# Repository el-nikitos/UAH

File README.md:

UAH
Драйвер двигателя и нагревателя

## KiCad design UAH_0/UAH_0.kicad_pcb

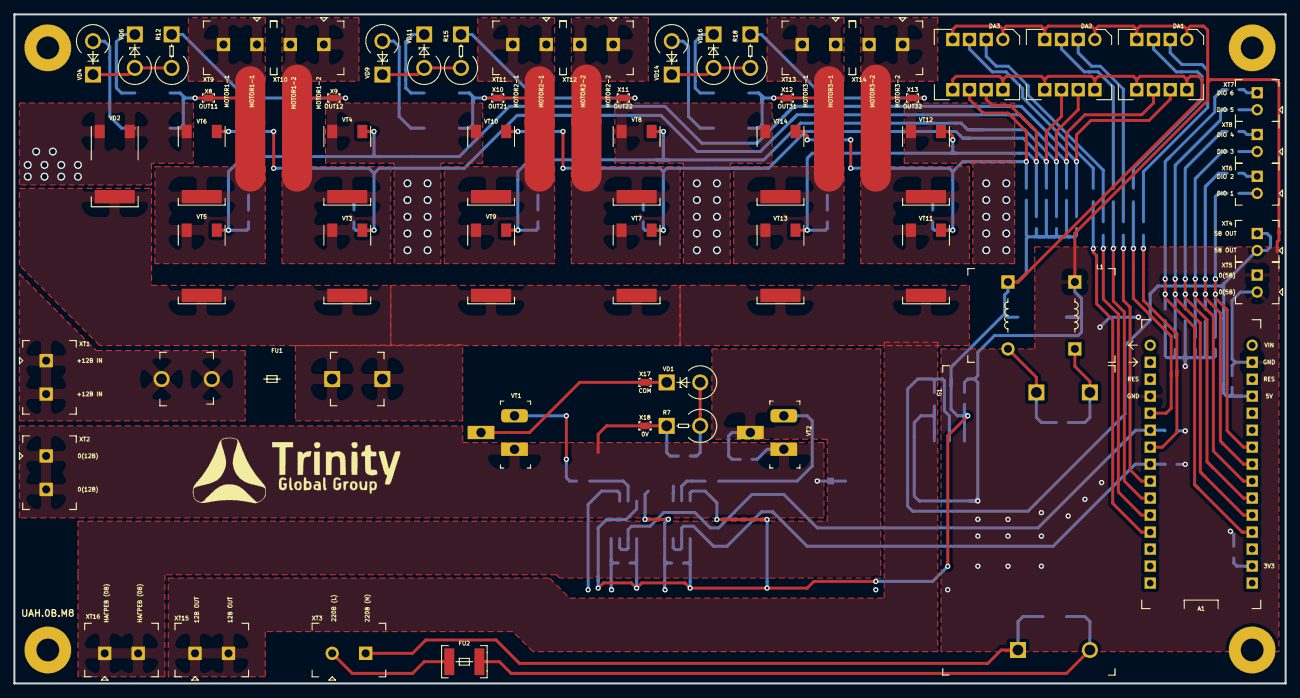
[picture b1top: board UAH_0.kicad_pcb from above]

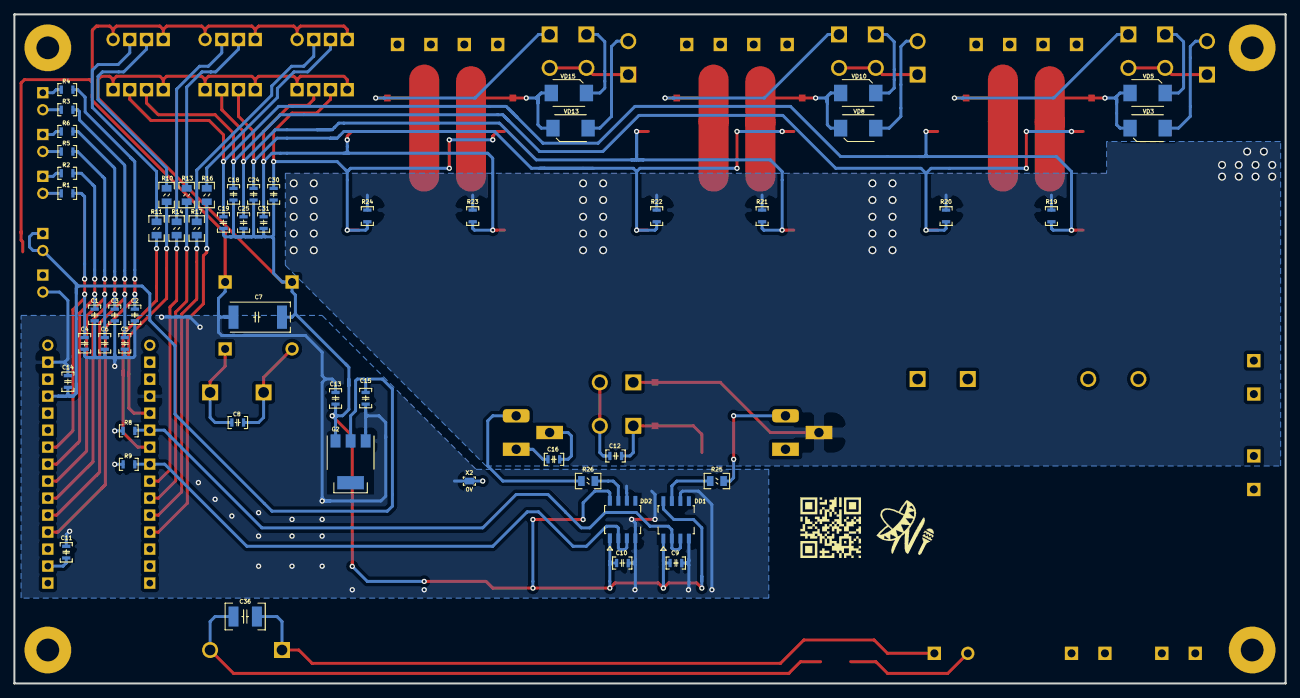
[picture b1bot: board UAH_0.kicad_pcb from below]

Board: 2 copper layers, 190.0 x 100.0 mm, 120 parts (57 on the bottom side), 74 nets.

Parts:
A1: модуль_arduino_nano; Arduino_nano
C1, C2, C3, C4, C5, C6, C9, C10, C11, C12, C16, C18, C19, C24, C25, C30, C31: Конденсатор_16В_0.1_мкФ+-10проц.; Конденсатор_SMD_К10-83(0603)
C7: Конденсатор_К53-56А-32В-22_мкФ+-10проц.; Конденсатор_тантал_SMD_m7343
C8, C13, C14, C15: Конденсатор_16В_10_мкФ+-10проц.; Конденсатор_SMD_К10-83(0603)
C36: Конденсатор_0.022мкФ_10проц_630В_1210; Конденсатор_SMD_1210
DA1, DA2, DA3: МОП-реле_КР293КП4_0; DIP8
DD1, DD2: Драйвер_FET-IGBT_IR2103STRPBF; SO-8
FU1: 30А_6.35х30; Предохранитель_6.35x30
FU2: Предохранитель_MF-MSMF010_0,1А_1812; Предохранитель_SMD_1812
G1: AC-DC-преобразователь_IRM-10-15; AC-DC_IRM-10-15
G2: стабилизатор_нерегулируемый_LM1117GS-5.0; Транзистор_NPN_SOT223
L1: Дроссель_B82731-T2451-A20_2х47мГн_0.45А_250В; Дроссель_B82731
R1, R2, R3, R4, R5, R6: Резистор_Р1-12-0,1_ум.-240_Ом±5%-Н-«А»; Резистор_SMD_0603-0,075_Вт
R7, R12, R15, R18: Резистор_CF-100_10_Ом_1Вт; резистор_C1-4-1_Вт_вертикальный
R8, R9, R19, R20, R21, R22, R23, R24: Резистор_10_кОм±5%_0,1Вт; Резистор_SMD_0603-0,075_Вт
R10, R11, R13, R14, R16, R17: Резистор_Р1-12-0,125-270_Ом±5%-Н-«А»; Резистор_SMD_0805_0,125Вт
R25, R26: Резистор_Р1-12-0,125-120_Ом±5%-Н-«А»; Резистор_SMD_0805_0,125Вт
VD1, VD4, VD6, VD9, VD11, VD14, VD16: Стабилитрон_1N5352BRLG_вертикальный; стабилитрон_DO-201_вертикальный
VD2: Диод_VS-20ETS08S-M3; Транзистор_N-канал_dpak
VD3, VD5, VD8, VD10, VD13, VD15: Диод_шоттки_SK16; Диод_SMB
VT1, VT2: MOSFET_N-канал_AUIRF3205Z; Транзистор_TO-220_COOLING
VT3, VT4, VT5, VT6, VT7, VT8, VT9, VT10, VT11, VT12, VT13, VT14: MOSFET_N-канал_STD60N3LH5; IGBT_dpak
X1: LOGO_NIKITOS_19х7; trinity_32x10
X2, X8, X9, X10, X11, X12, X13, X17, X18: Check_point; Пробник
X3, X4, X5, X6: Крепежное_отверстие_М3; Крепежное_Отверстие_под_М3
X7: LOGO_NIKITOS_19х7; ni_10x10
X14: LOGO_NIKITOS_19х7; El-nikitos_QR_10x10
XT1, XT2, XT3, XT9, XT10, XT11, XT12, XT13, XT14, XT15, XT16: Клеммник_х2_KLS2-300-5.00-02P-2S; Клеммник_х2_шаг5
XT4, XT5, XT6, XT7, XT8: Клеммник_х2_KLS2-300-5.00-02P-2S; Клеммник_х2_шаг2.54

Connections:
/0(12V)_IN: C16.2, VT1.3, VT2.3, X2.1, X18.2, XT2.1, XT2.2
/0(12V)_MC: A1.2, A1.19, C1.2, C2.2, C3.2, C4.2, C5.2, C6.2, C7.2, C9.2, C10.2, C11.2, C13.2, C14.2, C15.2, DA1.1, DA1.4, DA2.1, DA2.4, DA3.1, DA3.4, DD1.4, DD1.6, DD2.4, DD2.6, G2.1, L1.4, R8.2, R9.2, X2.2, XT5.1, XT5.2
/3V3: A1.14, C11.1
/5V_MC: A1.4, C14.1, C15.1, G2.2, XT4.1, XT4.2
/12V_FU: FU1.2, VD2.2, VT3.4, VT5.4, VT7.4, VT9.4, VT11.4, VT13.4, XT15.1, XT15.2
/12V_IN: FU1.1, XT1.1, XT1.2
/15V_MOSFET: C7.1, C9.1, C10.1, C13.1, C18.1, C19.2, C24.1, C25.2, C30.1, C31.2, DA1.5, DA1.8, DA2.5, DA2.8, DA3.5, DA3.8, DD1.1, DD1.8, DD2.1, DD2.8, G2.3, L1.6
/220_L: FU2.1, XT3.1
/220_N: C36.2, G1.N, XT3.2
/DRIVE_1: DD1.7, R25.1
/DRIVE_2: DD2.7, R26.1
/DRIVE_MC_1: A1.21, DD1.2, DD1.3, R8.1
/DRIVE_MC_2: A1.23, DD2.2, DD2.3, R9.1
/D_IN_1: R1.1, XT6.1
/D_IN_2: R2.1, XT6.2
/D_IN_3: R5.1, XT8.1
/D_IN_4: R6.1, XT8.2
/D_IN_5: R3.1, XT7.1
/D_IN_6: R4.1, XT7.2
/HEAT_OK: C16.1, VT2.2, XT16.1, XT16.2
/MC_DIN_1: A1.7, C4.1, R1.2
/MC_DIN_2: A1.8, C1.1, R2.2
/MC_DIN_3: A1.9, C6.1, R5.2
/MC_DIN_4: A1.10, C3.1, R6.2
/MC_DIN_5: A1.11, C5.1, R3.2
/MC_DIN_6: A1.12, C2.1, R4.2
/MOTOR_1_SPIN_1: A1.20, R10.1
/MOTOR_1_SPIN_2: A1.22, R11.1
/MOTOR_2_SPIN_1: A1.25, R13.1
/MOTOR_2_SPIN_2: A1.24, R14.1
/MOTOR_3_SPIN_1: A1.27, R16.1
/MOTOR_3_SPIN_2: A1.26, R17.1
/OUT_1_1: VT5.3, VT6.4, X8.1, XT9.1, XT9.2
/OUT_1_2: VT3.3, VT4.4, X9.2, XT10.1, XT10.2
/OUT_2_1: VT9.3, VT10.4, X10.1, XT11.1, XT11.2
/OUT_2_2: VT7.3, VT8.4, X11.2, XT12.1, XT12.2
/OUT_3_1: VT13.3, VT14.4, X12.1, XT13.1, XT13.2
/OUT_3_2: VT11.3, VT12.4, X13.2, XT14.1, XT14.2
/PWR_COMMON: R19.1, R20.1, R21.1, R22.1, R23.1, R24.1, VD2.1, VD2.3, VT1.2, VT4.3, VT6.3, VT8.3, VT10.3, VT12.3, VT14.3, X17.1
/PWR_COMMUTATION_1/CHANNEL_1: C18.2, DA1.6, R20.2, VT3.1, VT6.1
/PWR_COMMUTATION_1/CHANNEL_2: C19.1, DA1.7, R19.2, VT4.1, VT5.1
/PWR_COMMUTATION_2/CHANNEL_1: C24.2, DA2.6, R22.2, VT7.1, VT10.1
/PWR_COMMUTATION_2/CHANNEL_2: C25.1, DA2.7, R21.2, VT8.1, VT9.1
/sheet5F495C51/CHANNEL_1: C30.2, DA3.6, R24.2, VT11.1, VT14.1
/sheet5F495C51/CHANNEL_2: C31.1, DA3.7, R23.2, VT12.1, VT13.1
unnamed: C8.1, G1.+V, L1.1
unnamed: C8.2, G1.-V, L1.3
unnamed: C12.1, R7.1, VD1.1
unnamed: C12.2, R7.2, X18.1
unnamed: C36.1, FU2.2, G1.L
unnamed: DA1.2, R11.2
unnamed: DA1.3, R10.2
unnamed: DA2.2, R14.2
unnamed: DA2.3, R13.2
unnamed: DA3.2, R17.2
unnamed: DA3.3, R16.2
unnamed: R12.1, VD4.2, VD6.1
unnamed: R12.2, X9.1
unnamed: R15.1, VD9.2, VD11.1
unnamed: R15.2, X11.1
unnamed: R18.1, VD14.2, VD16.1
unnamed: R18.2, X13.1
unnamed: R25.2, VT1.1
unnamed: R26.2, VT2.1
unnamed: VD1.2, X17.2
unnamed: VD3.1, VD4.1
unnamed: VD3.2, VD5.1, X8.2
unnamed: VD5.2, VD6.2
unnamed: VD8.1, VD9.1
unnamed: VD8.2, VD10.1, X10.2
unnamed: VD10.2, VD11.2
unnamed: VD13.1, VD14.1
unnamed: VD13.2, VD15.1, X12.2
unnamed: VD15.2, VD16.2

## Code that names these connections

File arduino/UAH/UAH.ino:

#define MOTOR_1_SPIN_1  2
#define MOTOR_1_SPIN_2  4

#define MOTOR_2_SPIN_1  7
#define MOTOR_2_SPIN_2  6

#define MOTOR_3_SPIN_1  9
#define MOTOR_3_SPIN_2  8

#define MOTOR_DRIVE     3
#define HEAT_DRIVE      5

#define DIO_1           19
#define DIO_2           18
#define DIO_3           17
#define DIO_4           16
#define DIO_5           15
#define DIO_6           14

#define int_timer_overflow 100

int int_timer_count = 0,
    int_PWM_MOTOR_1 = 50,
    int_PWM_MOTOR_2 = 30;

int int_cicle_count = 0;

int int_delay_1,
    int_delay_2,
    int_delay_3,
    int_delay_4,
    int_delay_5,

    int_worltime_1,
    int_worltime_2,
    int_worltime_3,
    int_worltime_4,
    int_worltime_5,

    int_PWM_fill_1,
    int_PWM_fill_2,
    int_PWM_fill_3,
    int_PWM_fill_4,
    int_PWM_fill_5,
    

void setup() {

  Serial.begin(115200);

  pinMode(DIO_1, OUTPUT);
  digitalWrite(DIO_1, HIGH);

  digitalWrite(MOTOR_1_SPIN_1, LOW);
  digitalWrite(MOTOR_1_SPIN_2, LOW);
  pinMode(MOTOR_1_SPIN_1, OUTPUT);
  pinMode(MOTOR_1_SPIN_2, OUTPUT);

  digitalWrite(MOTOR_2_SPIN_1, LOW);
  digitalWrite(MOTOR_2_SPIN_2, LOW);  
  pinMode(MOTOR_2_SPIN_1, OUTPUT);
  pinMode(MOTOR_2_SPIN_2, OUTPUT);

  digitalWrite(MOTOR_3_SPIN_1, LOW);
  digitalWrite(MOTOR_3_SPIN_2, LOW);
  pinMode(MOTOR_3_SPIN_1, OUTPUT);
  pinMode(MOTOR_3_SPIN_2, OUTPUT);

  digitalWrite(MOTOR_DRIVE, LOW);
  digitalWrite(HEAT_DRIVE, LOW);
  pinMode(MOTOR_DRIVE, OUTPUT);
  pinMode(HEAT_DRIVE, OUTPUT);

  delay(1000);
}

void loop() {

  digitalWrite(MOTOR_DRIVE, HIGH);

  if (int_cicle_count < 500) {
    programm_PWM( MOTOR_1_SPIN_1, int_timer_count, int_PWM_MOTOR_1 );
  } 

  if (int_cicle_count == 500)  {
    turn_off_all();
  }

  if ( (int_cicle_count > 500) & (int_cicle_count < 1000) ) {
    programm_PWM( MOTOR_1_SPIN_2, int_timer_count, int_PWM_MOTOR_2 );
  }

  if ( (int_cicle_count >= 1000) & (int_cicle_count < 1500) ) {
    turn_off_all();
  }
  
  if (int_cicle_count >= 1500)  {
    int_cicle_count = 0;
  }


  delayMicroseconds( 100 ); 
  
  timer_counter();  // работа программного таймера ШИМ

  //Serial.println(long_cicle_count);

}

void programm_PWM( int PWM_channel, int counter, int PWM_fill ) {
  
  if (counter <= PWM_fill)  { digitalWrite(PWM_channel, HIGH); }
  else  { digitalWrite(PWM_channel, LOW); }

}

void turn_off_all() {
  digitalWrite(MOTOR_1_SPIN_1, LOW);
  digitalWrite(MOTOR_1_SPIN_2, LOW);
  digitalWrite(MOTOR_2_SPIN_1, LOW);
  digitalWrite(MOTOR_2_SPIN_2, LOW);
  digitalWrite(MOTOR_3_SPIN_1, LOW);
  digitalWrite(MOTOR_3_SPIN_2, LOW);
}

void timer_counter()  {
  
  int_timer_count++;
  
  if (int_timer_count >= int_timer_overflow) {
    
    int_timer_count = 0;
    int_cicle_count++;
  }

}

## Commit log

2020-08-06 Драйвер двигателя и нагревателя
2020-08-08 начата схема, не решен вопрос с драйверами, много УГО надо нарисовать
2020-08-09 обновлена схема управления движками
2020-08-12 закончена принципиальная схема, подготовлен мост и обвес на 1й канал
2020-08-13 расставлена силовая часть на 3 канала, нет управления и главных ключей
2020-08-15 не подведены управления DI, габарит определен
2020-08-16 закончена трассировка, надо добавить лого и маркировка, PDF обновлен
2020-08-16 добавлена маркировка, обновлены STEP, PDF, PNG, нет ЛОГО заказчика
2020-08-16 UAH_0B, готова плата +gerbers
2020-08-16 в схеме отражены позиции для BOM
2020-08-26 arduino - проверка функционирования
2020-08-26 за-define-ны ножки DIO
2020-08-31 ПО на комп
    подготовлено меню выбора последовательного порта, нужно добавить функционал кнопкам и добавить сетку выбора параметров
2020-09-01 ver.A0.1.M9 добавлен фокус на кнопки
2020-09-04 ver.A0.2.M9 добавлена сетка для ввода значений
2020-09-04 добавлены действия с полями и пояснения к областям рабочего поля
2020-09-05 ver.A0.4.M9 добавлена загрузка и сохранение параметров через json
2020-09-05 небольшие исправления в интерфейсе, заготовлен документ Тех. Описание
2021-02-21 исправления в прошивке
